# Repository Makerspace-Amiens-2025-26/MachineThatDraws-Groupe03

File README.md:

# 🤖 MachineThatDraws

**MachineThatDraws** est un traceur vectoriel automatisé (stylo sur papier) conçu de A à Z par le Groupe 3 constituer de Loïc Islam Louis et Tom. Capable de dessiner sur une surface utile de **170x140 mm**, cette machine se distingue par une indépendance logicielle totale : **toute la chaîne de contrôle et de génération de G-Code est gérée directement depuis un navigateur Web**, sans nécessiter l'installation de logiciels tiers.

---

##  Fonctionnalités Principales

-  **100% Web & Plug-and-Play :** Contrôle direct de la machine via le navigateur Chrome grâce à l'API **Web Serial**.
-  **Électronique Sur-Mesure :** Remplacement des solutions génériques par un microcontrôleur **ESP32 UNO** couplé à un **PCB "Fait Maison"** pour la puissance.
-  **Tête Hybride & Dessin Multicouleur :** Mouvement vertical (Axe Z) géré par un servomoteur et un système d'élastiques pour une pression constante. Supporte l'utilisation d'un stylo 4 couleurs (pauses automatiques pour changement manuel).
-  **Mécanique Fluide :** Guidage par tiges en acier de 6mm et bagues imprimées en **PETG-PTFE** (auto-lubrifiantes) pour un silence et une fluidité absolus.

---

##  Matériel & Ingénierie (Hardware)

### Architecture Cartésienne
La machine utilise une architecture en H (Axes X et Y indépendants) pour maximiser la rigidité, la précision géométrique et simplifier les calculs du firmware.
- **Moteurs :** NEMA 17 pour les axes X et Y (couple élevé, zéro perte de pas).
- **Axe Z :** Servomoteur ultra-léger (levée de 7 mm).
- **Transmission :** Courroies GT2 avec tendeurs micrométriques intégrés aux pièces 3D.
- **Impression 3D :** Pièces mécaniques imprimées en **PETG-CF** et **PLA-CF** (chargés en fibre de carbone) pour la rigidité structurelle. Assemblage robuste via des inserts filetés M3 en laiton.

### Électronique
- **Cerveau :** ESP32 UNO flashé avec le firmware **FluidNC** (évolution de GRBL).
- **Shield Maison :** PCB double couche routé spécifiquement pour le projet. Séparation stricte de la logique (5V/USB) et de la puissance (12V externe).
- **Sécurité :** Bouton d'Arrêt d'Urgence (BAU) et capteurs de fin de course (Endstops) mécaniques matériels avec offset de sécurité (5mm).

---

##  Suite Logicielle (Software)

L'équipe a fait le choix radical de coder ses propres "Slicers" et interfaces en **HTML, CSS et JavaScript pur**. La suite est divisée en 5 modules distincts :

### 1. Slicer Traceur (Reproduction d'Images)
Convertit n'importe quelle image matricielle (JPEG/PNG) en G-Code vectoriel. 
- Algorithme à **3 zones (Noir/Gris/Blanc)** : hachures croisées pour les zones sombres, lignes simples pour les zones grises, et épargne du papier pour les zones claires.
- Optimisation du chemin via l'algorithme du voyageur de commerce (TSP nearest neighbor).

### 2. Générateur Topographique (Art Génératif)
Crée des paysages uniques en temps réel en utilisant le **bruit de Perlin** (via `p5.js`).
- Tracé optimisé en zigzag pour éviter de lever le stylo.
- Filtrage intelligent des points superflus pour alléger le fichier G-Code.

### 3. Studio Texte CNC (Word Vectoriel)
Transforme la CNC en machine à écrire. Un véritable éditeur multi-calques qui utilise la fonction `textToPoints` pour convertir des polices TTF en coordonnées (X, Y) traçables par le stylo. Gère l'inclinaison par rotation trigonométrique.

### 4. Slicer Visage (Algorithme "Squiggle")
Un algorithme spécifique pour le portrait. Simule les ombres d'un visage en modulant l'amplitude et la fréquence d'une **onde sinusoïdale** continue, créant un effet de gravure organique.

### 5. Studio Musique CNC (Lecteur MIDI)
Détourne la fonction première de la machine pour lui faire jouer de la musique ! Convertit des fichiers `.mid` en fréquences de rotation pour faire "chanter" les moteurs pas-à-pas tout en gérant un algorithme de rebond balistique pour rester dans les limites du plateau.

### 6. Manuel
Il permet de contrôler la machine manuellement avec les flèches du clavier et la barre d'espace. Grâce à lui, nous pouvons régler la vitesse idéale pour la machine.

---

##  Comment l'utiliser ?

1. **Branchement :** Reliez l'alimentation 12V au boîtier et connectez le câble USB à votre PC.
2. **Interface :** Ouvrez l'interface Web (fichiers HTML) dans un navigateur compatible Web Serial (ex: Google Chrome).
3. **Connexion :** Cliquez sur "Connecter USB" et sélectionnez le port série de l'ESP32 (BaudRate : 115200).
4. **Initialisation :** Lancez la procédure de *Homing* (`$H`) pour que la machine trouve son point 0,0 via les endstops.
5. **Génération & Dessin :** Choisissez un des 5 modules, paramétrez votre création en temps réel sur le canvas, puis cliquez sur "Lancer l'impression" !

---

## 👥 Équipe & Crédits

- Projet réalisé par le **Groupe 3** constituer de Loïc Islam Louis et Tom dans le cadre d'un projet académique.
- **Librairies utilisées :** `p5.js` (rendu canvas et mathématiques), `imagetracer.js` (vectorisation), `@tonejs/midi` (parsing musical).

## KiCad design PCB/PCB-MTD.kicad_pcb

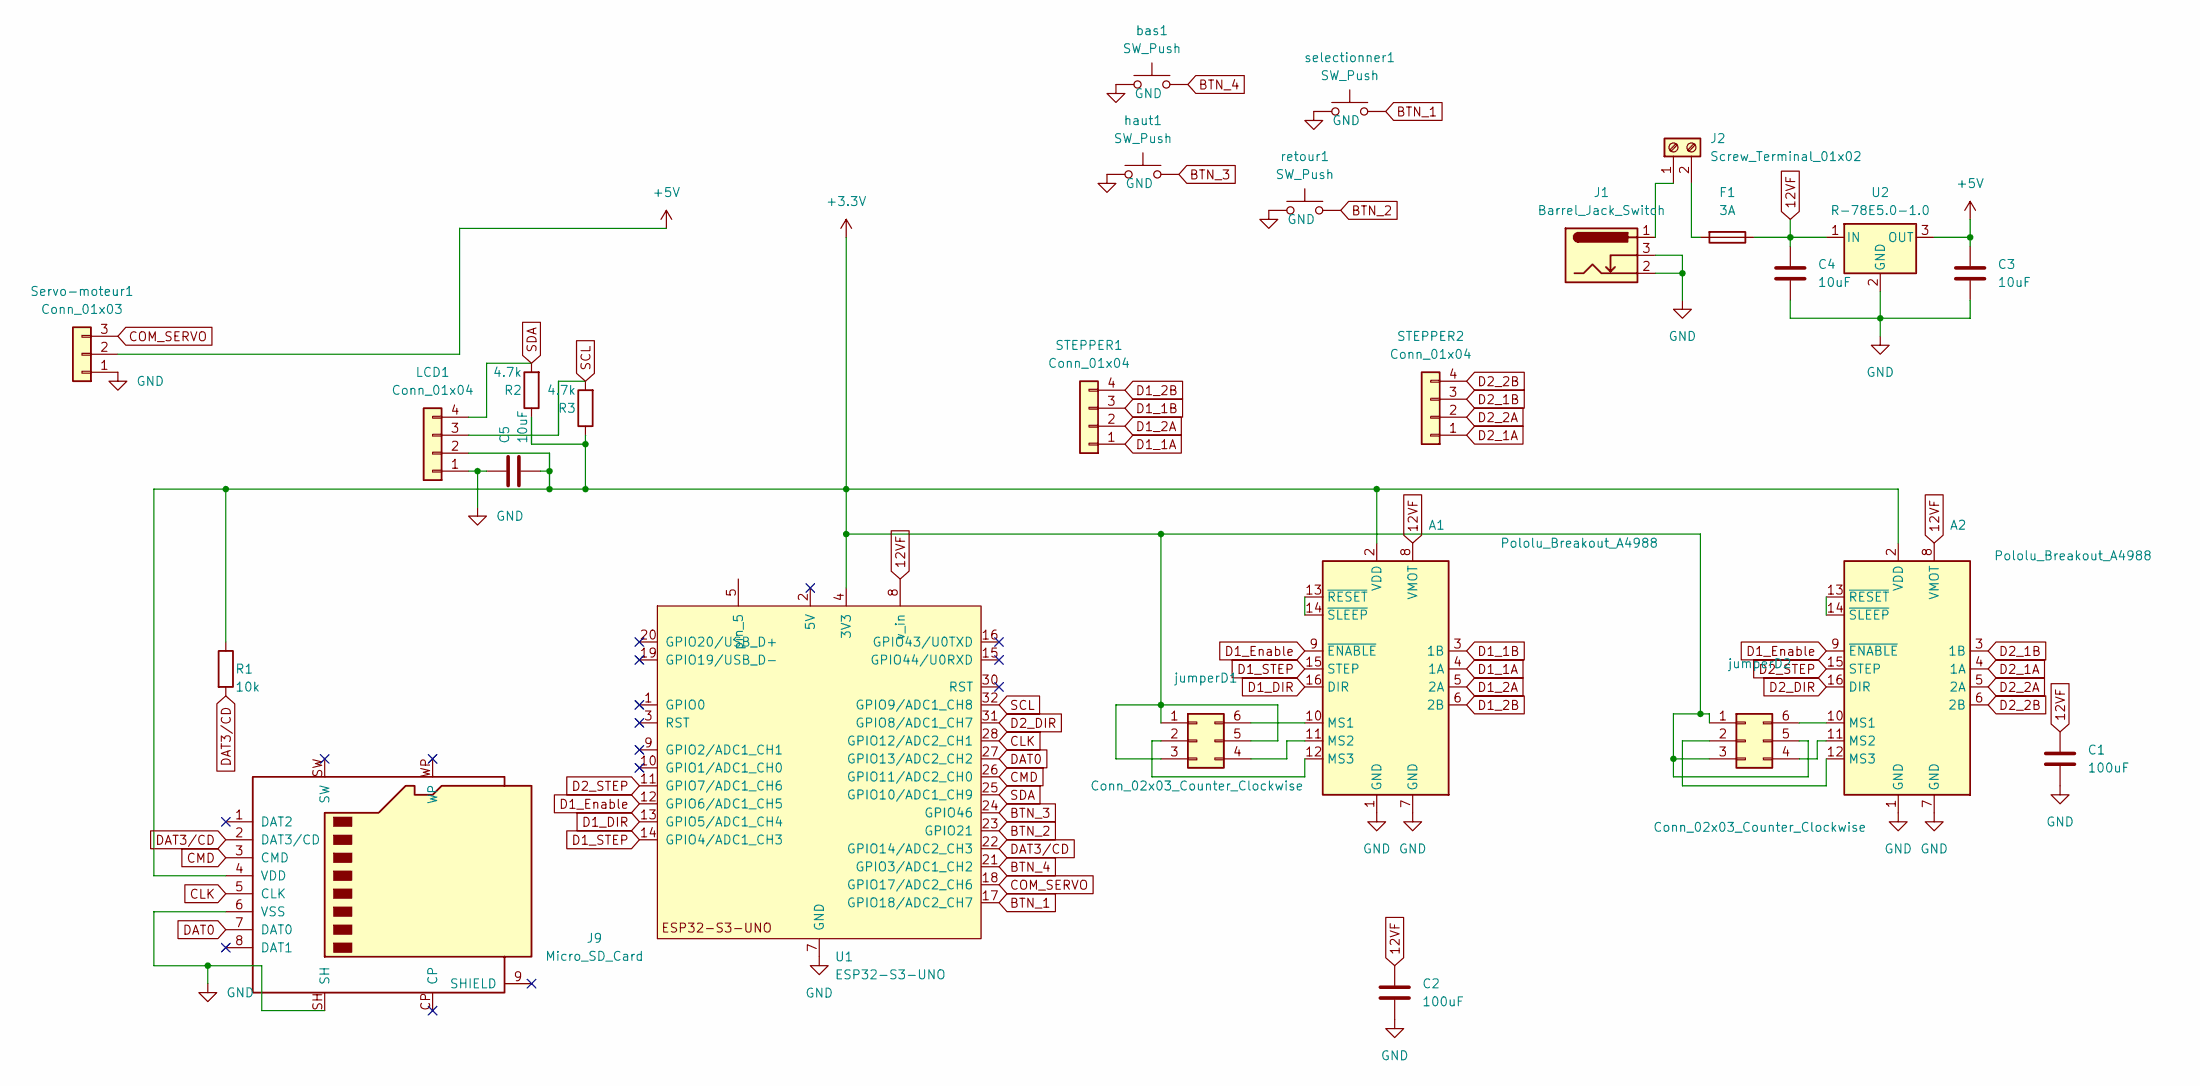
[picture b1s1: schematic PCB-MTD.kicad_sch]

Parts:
A1, A2: Pololu_Breakout_A4988; Pololu_Breakout-16_15.2x20.3mm
C1, C2: 100uF; CP_Elec_6.3x5.4
C3, C4, C5: 10uF; C_1206_3216Metric_Pad1.33x1.80mm_HandSolder
F1: 3A; Fuseholder_Blade_Mini_Keystone_3568
J1: Barrel_Jack_Switch; BarrelJack_Horizontal
J2: Screw_Terminal_01x02; TerminalBlock_Phoenix_MKDS-1,5-2-5.08_1x02_P5.08mm_Horizont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
J9: Micro_SD_Card; SD_Hirose_DM1AA_SF_PEJ82
LCD1: Conn_01x04; PinHeader_1x04_P2.54mm_Vertical
R1: 10k; R_0805_2012Metric_Pad1.20x1.40mm_HandSolder
R2, R3: 4.7k; R_0805_2012Metric_Pad1.20x1.40mm_HandSolder
STEPPER1, STEPPER2: Conn_01x04; PinHeader_1x04_P2.54mm_Vertical
Servo-moteur1: Conn_01x03; PinHeader_1x03_P2.54mm_Vertical
U1: ESP32-S3-UNO; ESP_S3_UNO
U2: R-78E5.0-1.0; Converter_DCDC_RECOM_R-78E-0.5_THT
bas1: SW_Push; SW_Tactile_Straight_KSA0Axx1LFTR
haut1: SW_Push; SW_Tactile_Straight_KSA0Axx1LFTR
jumperD1, jumperD2: Conn_02x03_Counter_Clockwise; PinHeader_2x03_P2.54mm_Vertical
retour1: SW_Push; SW_Tactile_Straight_KSA0Axx1LFTR
selectionner1: SW_Push; SW_Tactile_Straight_KSA0Axx1LFTR

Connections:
12VF: A1.8 (VMOT), A2.8 (VMOT), C1.1, C2.1, C4.1, F1.1, U1.8 (v_in), U2.1 (IN)
+3.3V: A1.2 (VDD), A2.2 (VDD), C5.2, J9.4 (VDD), LCD1.2, R1.1, R2.1, R3.1, U1.4 (3V3), jumperD1.1, jumperD1.3, jumperD1.5, jumperD2.1, jumperD2.3, jumperD2.5
+5V: C3.1, Servo-moteur1.2, U2.3 (OUT)
BTN_1: U1.17 (GPIO18/ADC2_CH7), selectionner1.2
BTN_2: U1.23 (GPIO21), retour1.2
BTN_3: U1.24 (GPIO46), haut1.2
BTN_4: U1.21 (GPIO3/ADC1_CH2), bas1.2
CLK: J9.5 (CLK), U1.28 (GPIO12/ADC2_CH1)
CMD: J9.3 (CMD), U1.26 (GPIO11/ADC2_CH0)
COM_SERVO: Servo-moteur1.3, U1.18 (GPIO17/ADC2_CH6)
D1_1A: A1.4 (1A), STEPPER1.1
D1_1B: A1.3 (1B), STEPPER1.3
D1_2A: A1.5 (2A), STEPPER1.2
D1_2B: A1.6 (2B), STEPPER1.4
D1_DIR: A1.16 (DIR), U1.13 (GPIO5/ADC1_CH4)
D1_Enable: A1.9 (~ENABLE), A2.9 (~ENABLE), U1.12 (GPIO6/ADC1_CH5)
D1_STEP: A1.15 (STEP), U1.14 (GPIO4/ADC1_CH3)
D2_1A: A2.4 (1A), STEPPER2.1
D2_1B: A2.3 (1B), STEPPER2.3
D2_2A: A2.5 (2A), STEPPER2.2
D2_2B: A2.6 (2B), STEPPER2.4
D2_DIR: A2.16 (DIR), U1.31 (GPIO8/ADC1_CH7)
D2_STEP: A2.15 (STEP), U1.11 (GPIO7/ADC1_CH6)
DAT0: J9.7 (DAT0), U1.27 (GPIO13/ADC2_CH2)
DAT3/CD: J9.2 (DAT3/CD), R1.2, U1.22 (GPIO14/ADC2_CH3)
GND: A1.1 (GND), A1.7 (GND), A2.1 (GND), A2.7 (GND), C1.2, C2.2, C3.2, C4.2, C5.1, J1.2, J1.3, J9.6 (VSS), J9.SH, LCD1.1, Servo-moteur1.1, U1.6 (GND), U1.7 (GND), U1.29 (GND), U2.2 (GND), bas1.1, haut1.1, retour1.1, selectionner1.1
unnamed: A1.10 (MS1), jumperD1.6
unnamed: A1.11 (MS2), jumperD1.4
unnamed: A1.12 (MS3), jumperD1.2
unnamed: A1.13 (~RESET), A1.14 (~SLEEP)
unnamed: A2.10 (MS1), jumperD2.6
unnamed: A2.11 (MS2), jumperD2.4
unnamed: A2.12 (MS3), jumperD2.2
unnamed: A2.13 (~RESET), A2.14 (~SLEEP)
unnamed: J1.1, J2.1
unnamed: F1.2, J2.2
SCL: LCD1.3, R3.2, U1.32 (GPIO9/ADC1_CH8)
SDA: LCD1.4, R2.2, U1.25 (GPIO10/ADC1_CH9)

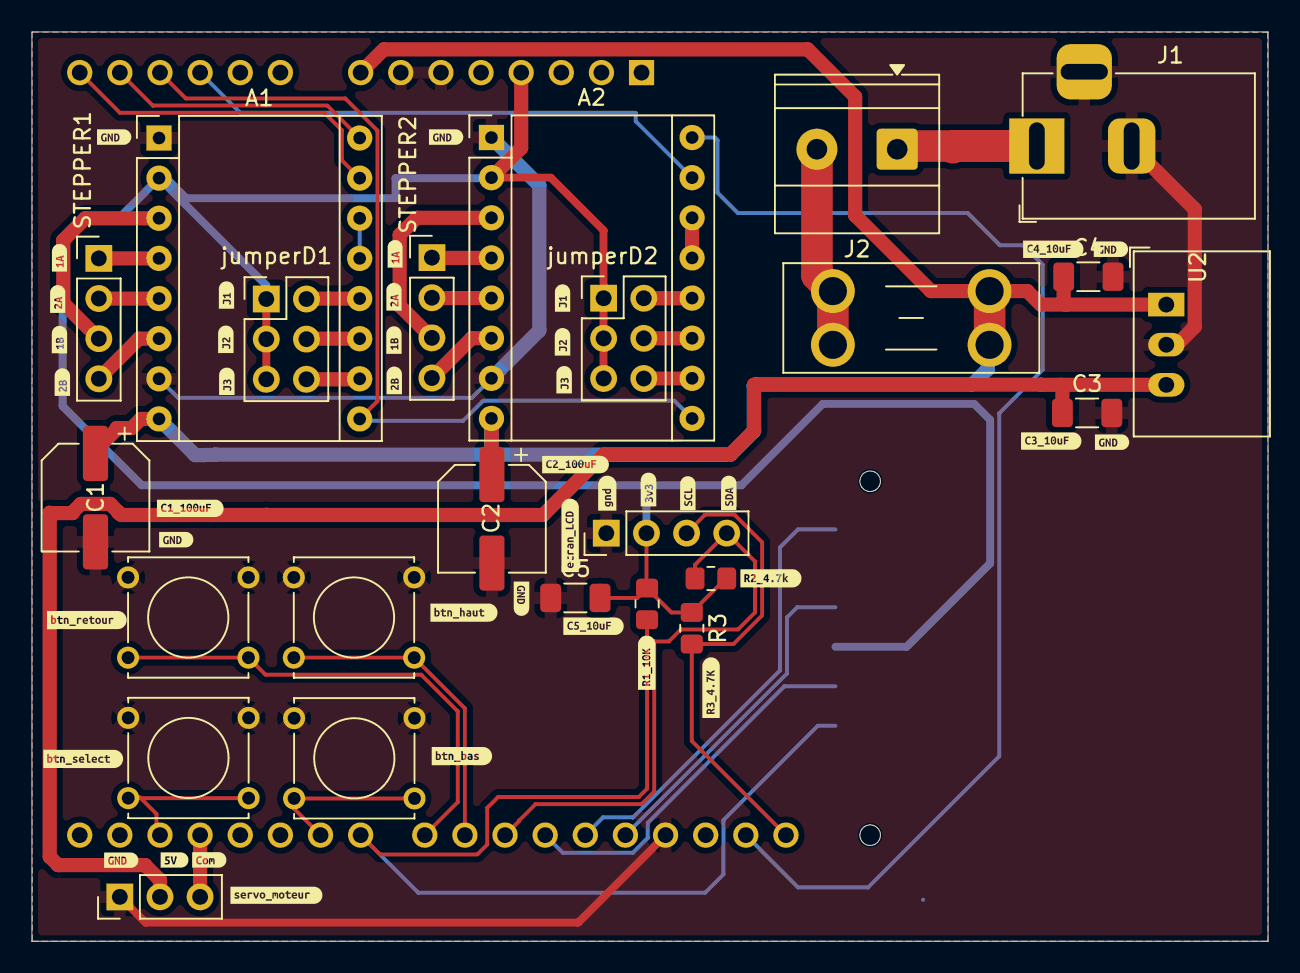
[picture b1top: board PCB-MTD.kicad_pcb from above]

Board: 2 copper layers, 78.2 x 57.6 mm, 67 parts (1 on the bottom side), 38 nets.

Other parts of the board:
kibuzzard-69E8AB7B: G***; kibuzzard-69E8AB7B
kibuzzard-69E8AB48: G***; kibuzzard-69E8AB48
kibuzzard-69E8AB94: G***; kibuzzard-69E8AB94
kibuzzard-69E8ABA4: G***; kibuzzard-69E8ABA4
kibuzzard-69E8ABD2: G***; kibuzzard-69E8ABD2
kibuzzard-69E8ABED: G***; kibuzzard-69E8ABED
kibuzzard-69E8ABFE: G***; kibuzzard-69E8ABFE
kibuzzard-69E8AC2D: G***; kibuzzard-69E8AC2D
kibuzzard-69E8AC3C: G***; kibuzzard-69E8AC3C
kibuzzard-69E8AC9A: G***; kibuzzard-69E8AC9A
kibuzzard-69E8ACB2: G***; kibuzzard-69E8ACB2
kibuzzard-69E8ACC9: G***; kibuzzard-69E8ACC9
kibuzzard-69E8AD3B, kibuzzard-69E8AD3B#2: G***; kibuzzard-69E8AD3B
kibuzzard-69E8AD47, kibuzzard-69E8AD47#2: G***; kibuzzard-69E8AD47
kibuzzard-69E8AD54, kibuzzard-69E8AD54#2: G***; kibuzzard-69E8AD54
kibuzzard-69E8ADAF, kibuzzard-69E8ADAF#2: G***; kibuzzard-69E8ADAF
kibuzzard-69E8ADD5, kibuzzard-69E8ADD5#2: G***; kibuzzard-69E8ADD5
kibuzzard-69E8AE0E: G***; kibuzzard-69E8AE0E
kibuzzard-69E8AE4C: G***; kibuzzard-69E8AE4C
kibuzzard-69E8AE7F: G***; kibuzzard-69E8AE7F
kibuzzard-69E8AE60: G***; kibuzzard-69E8AE60
kibuzzard-69E8AE92: G***; kibuzzard-69E8AE92
kibuzzard-69E8AEC7: G***; kibuzzard-69E8AEC7
kibuzzard-69E8AEDA, kibuzzard-69E8AEDA#2: G***; kibuzzard-69E8AEDA
kibuzzard-69E8AEFD: G***; kibuzzard-69E8AEFD
kibuzzard-69E8AF1C: G***; kibuzzard-69E8AF1C
kibuzzard-69E8B027, kibuzzard-69E8B027#2: G***; kibuzzard-69E8B027
kibuzzard-69E8C7AB: G***; kibuzzard-69E8C7AB
kibuzzard-69E8C7B2: G***; kibuzzard-69E8C7B2
kibuzzard-69E8C7BE: G***; kibuzzard-69E8C7BE
kibuzzard-69E8C8E3: G***; kibuzzard-69E8C8E3
kibuzzard-69E8C83B: G***; kibuzzard-69E8C83B
kibuzzard-69E8C827: G***; kibuzzard-69E8C827
kibuzzard-69E8C830: G***; kibuzzard-69E8C830

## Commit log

2026-02-09 Objectif
2026-02-09 Markdown index
2026-02-09 Modele3d
2026-02-09 Correction
2026-02-09 Correction Titre
2026-02-24 Video
2026-04-10 PCB fait erreur corriger
2026-04-10 Create test
2026-04-24 Validation PCB pour production
    Attention :
    - Incohérence alimentation Driver et Jumper microstepping
    - Resistance de tirage haut SCL SDA
2026-04-25 Test Html
2026-04-25 test html 2
2026-04-25 Html 3
2026-04-25 Suppression des actions Jekyll
2026-04-25 Ajout du workflow pour déployer le site HTML
2026-04-25 clean
2026-04-25 pcb clean
2026-04-27 fix wiring problems
2026-05-11 Documentation
2026-05-11 Ajoute Manuel
2026-05-11 manuel
2026-05-11 Correctif
2026-05-11 Revise README for MachineThatDraws project
    Updated project description and features in README.
2026-05-11 Update README
    Corrected team member names and clarified project context.
2026-05-20 ajoute reprise, optimisation et importation de gcode
2026-05-20 correctif visage déormation ratio
2026-05-20 orthographe menu.js
2026-05-20 nouveau style + optimisation
2026-05-20 New Tree
2026-05-20 clean fichiers pcb
2026-05-21 fix pour reprise coupure courant + ajout yaml fluid nc
2026-05-21 rename
2026-05-21 config fluidnc
2026-05-21 fin fluid nc
2026-05-26 maj doc 1
2026-05-26 maj doc 2
2026-05-26 maj doc 3
2026-05-26 maj doc 4
2026-05-26 maj doc 5
2026-05-29 fluidnc
2026-06-01 speed
2026-06-05 ajout video + page logiciel manuel
2026-06-06 Ajoute poster
2026-06-06 Ajoute poster png
2026-06-06 Correctif video 1
2026-06-06 Correctif video 2
2026-06-06 Ajout slicer 6 dans reeadme
